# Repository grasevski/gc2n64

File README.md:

# gc2n64
Gamecube controller to N64 adapter. Dependencies:

 * [avra](https://github.com/Ro5bert/avra): `apt install avra` - AVR assembler
 * [avrdude](https://github.com/avrdudes/avrdude): `apt install avrdude` - to flash program to ATTiny
 * [KiCAD](https://www.kicad.org/): `apt install kicad` - for schematic
 * [ATTiny9](https://www.microchip.com/en-us/product/attiny9): SOT-23-6 is used for running the code. Attiny 25/45/85 can be used instead if preferred.

Usage:

```
# Build
make

# Flash to attiny9
make flash

# Delete build output
make clean
```

The KiCAD schematic is in the schematic directory. It has a TC2030-NL footprint for flashing and debugging. It is designed to be wired to two respective extension cables for gamecube and n64. Then it can be heatshrunk for neatness and stress relief.

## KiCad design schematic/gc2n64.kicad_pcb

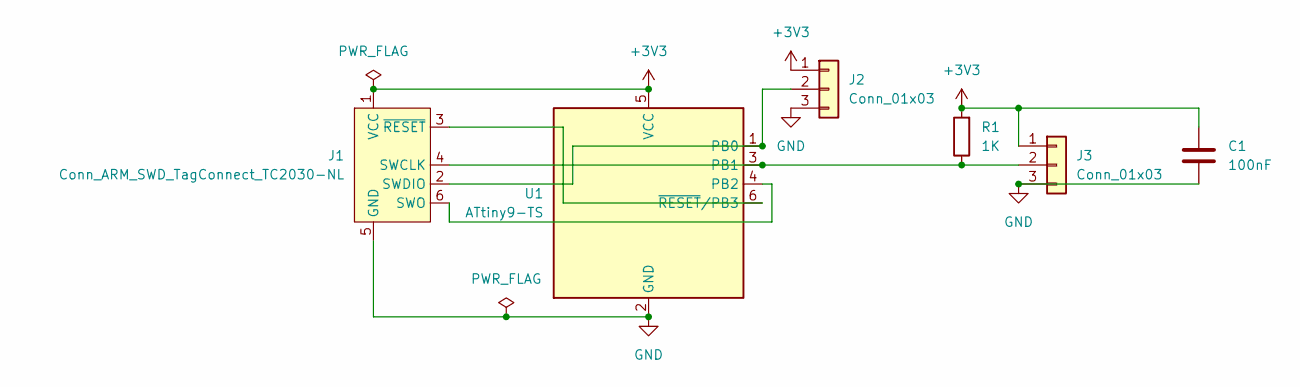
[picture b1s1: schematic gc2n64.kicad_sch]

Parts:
C1: 100nF; C_0402_1005Metric
J1: Conn_ARM_SWD_TagConnect_TC2030-NL; Tag-Connect_TC2030-IDC-NL_2x03_P1.27mm_Vertical
J2, J3: Conn_01x03; SolderWire-0.1sqmm_1x03_P3.6mm_D0.4mm_OD1mm_Relief2x
R1: 1K; R_0402_1005Metric
U1: ATtiny9-TS; SOT-23-6

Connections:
+3V3: C1.1, J1.1 (VCC), J2.1, J3.1, R1.2, U1.5 (VCC)
GND: C1.2, J1.5 (GND), J2.3, J3.3, U1.2 (GND)
unnamed: J1.4 (SWCLK), J3.2, R1.1, U1.3 (PB1)
unnamed: J1.2 (SWDIO), J2.2, U1.1 (PB0)
unnamed: J1.6 (SWO), U1.4 (PB2)
unnamed: J1.3 (~RESET), U1.6 (~RESET/PB3)

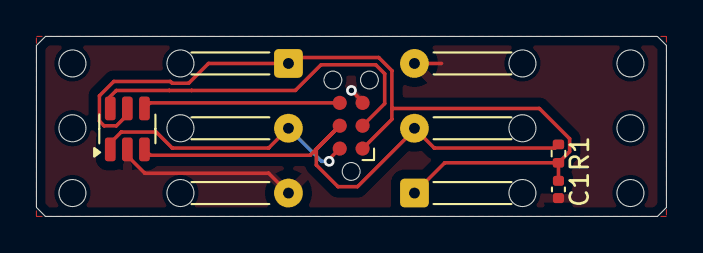
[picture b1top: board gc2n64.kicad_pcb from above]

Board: 2 copper layers, 35.0 x 10.0 mm, 6 parts (0 on the bottom side), 6 nets.

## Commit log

2025-08-13 feat(code): first draft
2025-08-26 fix(timing): adjust OSCCAL based on n64 timing
    Timing needs some fine tuning. Power down sleep has too much latency.
    Also, watchdog timer tolerance is too loose. Change to idle sleep, use
    timer0, and calibrate internal oscillator based on n64 request bit
    timing.
2025-09-22 feat(design): revision 2
    Refactored the design to work with either attiny9 or attiny25, using a
    basic hardware abstraction layer. So that the PCB can have a tagconnect
    footprint rather than excessive through holes and plugging and
    unplugging of attiny85 into a socket.
2025-10-27 fix(n64): n64 side working
    Gamecube controller is being polled, but it is not responding.
2025-10-27 chore(refactor): remove unused constants
2025-11-09 chore(testing): n64 side works
    Gamecube side is sending, but needs to be rewired to see if it will
    receive a response.
2025-11-15 controller working, but pressing random buttons
2025-11-18 Analog and c buttons working.
2025-11-22 everything still working except gamecube a b start
2025-11-23 Its alaaiiivee!
2025-11-23 calibrate on startup
2025-11-23 formatting
2025-11-23 documentation
